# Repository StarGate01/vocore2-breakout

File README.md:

# vocore2-breakout

KiCad breakout board for the VoCore2 module (MT7628AN SoC).

## JTAG Connector (J-Link EDU Mini)

J6 is a 2×5 1.27 mm pitch header wired to the standard 9-pin ARM Cortex debug connector used by the J-Link EDU Mini.

| Pin | Signal | Notes |
|-----|--------|-------|
| 1 | `+3V3` | VTref - sense only, do not power board from here |
| 2 | `JTAG_TMS` | MT7628 `GPIO41` / `EPHY_LED2_N_JTMS` |
| 3 | `GND` | |
| 4 | `JTAG_CLK` | MT7628 `GPIO40` / `EPHY_LED3_N_JTCLK` |
| 5 | `GND` | |
| 6 | `JTAG_TDO` | MT7628 `GPIO43` / `EPHY_LED0_N_JTDO` |
| 7 | NC | KEY position - no pin on J-Link EDU Mini |
| 8 | `JTAG_TDI` | MT7628 `GPIO42` / `EPHY_LED1_N_JTDI` |
| 9 | `JTAG_TRST` | MT7628 `GPIO39` / `EPHY_LED4_N_JTRST_N` |
| 10 | `RESET` | MT7628 pin 138 / `PORST_N` (system reset, active-low) |

### J-Link EDU Mini reset pin specialities

The J-Link EDU Mini uses the **9-pin Cortex-M variant** of the connector, not the full 20-pin JTAG header:

- **Pin 7** is a physical key (no pin present). Not connected.
- **Pin 9** is repurposed by Segger as **nTRST** (JTAG TAP reset, active-low). In the standard Cortex-M spec pin 9 is NC; Segger uses it to support targets that need hardware TRST. Wire to `JTRST_N` (`GPIO39`).
- **Pin 10** is **nRESET** (system reset, active-low). Wire to `PORST_N`.

`WDT_RST_N` (`GPIO37` / MT7628 pin 137) appears adjacent to `PORST_N` and `JTRST_N` on the VoCore2 right-side connector and was considered for pin 9.

The vendor's JTAG how-to uses `WDT_RST_N` as "TRST" in their OpenOCD `sysfsgpio` config. This works because their setup is one VoCore2 bit-banging GPIOs to debug another - the host just needs two GPIO outputs to toggle, and driving `WDT_RST_N` low from an external GPIO triggers a full chip reset which also resets the JTAG TAP. OpenOCD's `sysfsgpio` driver doesn't care what hardware the signal is physically connected to; it just toggles the GPIO.

The J-Link is a hardware probe that follows the ARM Cortex debug connector spec strictly: pin 9 (`nTRST`) is driven by J-Link silicon to reset *only the JTAG TAP*, and the probe asserts and de-asserts it independently during normal debug sessions. If pin 9 connects to `WDT_RST_N`, every `nTRST` assertion by the J-Link triggers a full watchdog system reset, killing the debug session. `WDT_RST_N` is also a chip *output* when the watchdog fires, so the J-Link driving it creates a bus conflict. `JTRST_N` (`GPIO39`) resets only the TAP and has no output driver conflict.

### Pull-up resistors

All five JTAG signals (`TMS`, `TCK`, `TDI`, `TDO`, `TRST`) need pull-ups to 3V3. `RESET` (`PORST_N`) does not need external pull-ups from the breakout.

### OpenOCD configuration

OpenOCD requires third-party target scripts for the MT7628 - the standard script directory does not include this SoC. Clone [mtk-openwrt/openocd-scripts](https://github.com/mtk-openwrt/openocd-scripts) and point `OPENOCD_SCRIPTS` at it. This provides `mt7628.cfg` along with the `cpu_pll_init` and `dram_init` TCL helpers needed to bring up the PLL and DDR2 after halting the CPU via JTAG.

```sh
openocd -f interface/jlink.cfg \
        -c "transport select jtag" \
        -c "adapter speed 100" \
        -c "reset_config trst_and_srst separate srst_nogate connect_assert_srst" \
        -f mt7628.cfg \
        -c "init" \
        -c "reset halt" \
        -c "wait_halt 10000"
```

`adapter speed 100` - the MT7628 PLL is not running at reset; the JTAG clock source is the raw 40 MHz crystal. 100 kHz is conservative enough to be reliable in that window.

`reset_config trst_and_srst separate srst_nogate connect_assert_srst` - `connect_assert_srst` holds SRST (PORST_N) asserted when OpenOCD first connects, keeping the system in reset while the JTAG TAP initializes. `srst_nogate` keeps TCK running during SRST so OpenOCD can set the `EJTAGBOOT` instruction before releasing SRST. When SRST releases, the CPU starts with EJTAGBOOT active, enters the EJTAG debug ROM, and halts before its first instruction.

## TXD1 JTAG mode selector

MT7628 `GPIO13` / `TXD1` (VoCore2 pad `PR01`) is sampled at power-on reset to determine whether the `EPHY_LED` pins (`GPIO39`–`GPIO43`) operate as Ethernet LEDs or as the JTAG interface.

| `TXD1` at boot | Mode |
|----------------|------|
| HIGH (3V3) | Normal - `EPHY_LED` pins as Ethernet LEDs, **JTAG disabled** |
| LOW (GND) | **JTAG enabled** - `EPHY_LED` pins as `TMS`/`TCK`/`TDI`/`TDO`/`TRST` |

`JP1` is a 3-pin jumper with 4.7 kΩ resistors on both options:

| `JP1` position | `TXD1` | JTAG |
|---------------|--------|------|
| 1-2 ("GPIO", default) | HIGH via `R1` (4K7 to `+3V3`) | Disabled |
| 2-3 ("JTAG") | LOW via `R2` (4K7 to `GND`) | **Enabled** |

Warning: JTAG mode breaks SD/eMMC on the EPHY pads.`TXD1` low (`DBG_JTAG_MODE=0`) does more than swap the `EPHY_LED` pins to JTAG, it puts the whole EPHY block into JTAG/debug state. If SD/eMMC is then muxed onto the EPHY pads ("IoT" mode, e.g. VoCore2's SD lines), the card stops responding. This is a hardware mutual-exclusion, not a software setting, JTAG and SD-on-EPHY cannot be used at the same time. Change the jumper after flashing to put the board into normal operation.

### VoCore2 module modification required

The stock VoCore2 module has **`R9` populated** (pull-up, 4.7 kΩ to 3V3) which holds `TXD1` high and disables JTAG. To use JTAG:

1. Remove `R9` from the VoCore2 module (eliminates the internal pull-up).
2. Set `JP` to position 2-3 on the breakout.

The breakout `JP` then has sole control over `TXD1` with no internal resistor fighting it. Leaving `R9` on the module while setting `JP` to 2-3 creates a voltage divider (~1.65 V, undefined logic level).

The original VoCore2 JTAG how-to describes moving `R9` to the `R6` footprint (a pull-down). With `R9` removed entirely and `JP` at 2-3, the effect is the same.

## Fabrication

Gerber files are in the `gerber/` directory and can be sent directly to a PCB manufacturer.

Before assembly, it is recommended to bake the VoCore2 module at 120 °C for at least 12 hours to drive out moisture. However it works just as well without.

The VoCore2 module must be reflowed using hot air, do not use a soldering iron. The DDR2 on the module is ESD-sensitive and iron leakage current can cause permanent damage. Reflow temperature must not exceed 260 °C for more than 10 seconds.

The resistors can be reflowed together with the VoCore2 module or soldered normally with an iron. The through-hole pin headers are soldered normally. Take special care with the JTAG header (J6): it uses a 1.27 mm pitch fine-pitch header where adjacent pins are easy to bridge accidentally. Inspect with a loupe or microscope after soldering.

## References

- [J-Link EDU Mini KB](https://kb.segger.com/J-Link_EDU_Mini)
- [9-pin JTAG/SWD connector](https://kb.segger.com/9-pin_JTAG/SWD_connector)
- [VoCore2 pinout](https://vocore.io/v2.html)
- [VoCore2 JTAG how-to](https://vonger.cn/?p=14897)

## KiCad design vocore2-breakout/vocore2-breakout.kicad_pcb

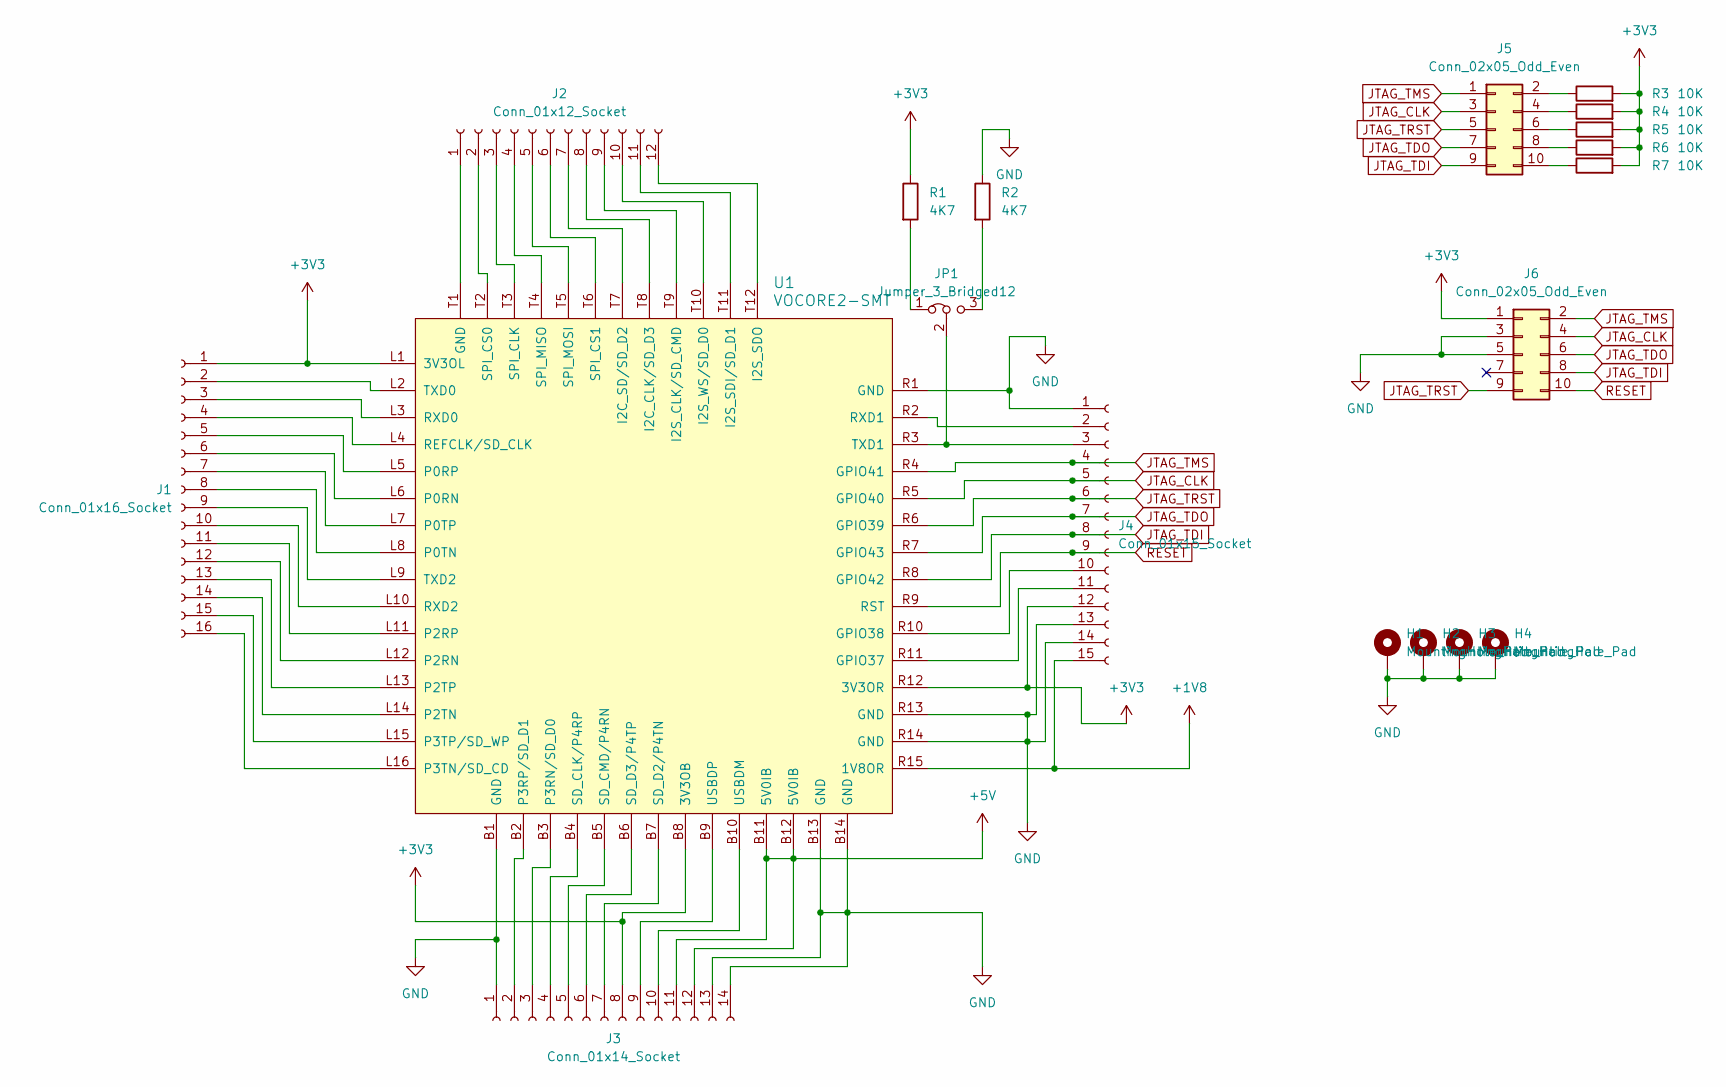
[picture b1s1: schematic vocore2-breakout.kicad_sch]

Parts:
H1, H2, H3, H4: MountingHole_Pad; MountingHole_3.2mm_M3_DIN965_Pad
J1: Conn_01x16_Socket; PinHeader_1x16_P2.54mm_Vertical
J2: Conn_01x12_Socket; PinHeader_1x12_P2.54mm_Vertical
J3: Conn_01x14_Socket; PinHeader_1x14_P2.54mm_Vertical
J4: Conn_01x15_Socket; PinHeader_1x15_P2.54mm_Vertical
J5: Conn_02x05_Odd_Even; PinHeader_2x05_P2.54mm_Vertical
J6: Conn_02x05_Odd_Even; PinHeader_2x05_P1.27mm_Vertical
JP1: Jumper_3_Bridged12; PinHeader_1x03_P2.54mm_Vertical
R1, R2: 4K7; R_0805_2012Metric_Pad1.20x1.40mm_HandSolder
R3, R4, R5, R6, R7: 10K; R_0805_2012Metric_Pad1.20x1.40mm_HandSolder
U1: VOCORE2-SMT

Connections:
+1V8: J4.15, U1.R15 (1V8OR)
+3V3: J1.1, J3.8, J4.12, J6.1, R1.1, R3.2, R4.2, R5.2, R6.2, R7.2, U1.B8 (3V3OB), U1.L1 (3V3OL), U1.R12 (3V3OR)
+5V: J3.11, J3.12, U1.B11 (5V0IB), U1.B12 (5V0IB)
GND: H1.1 (1_1), H2.1 (1_1), H3.1 (1_1), H4.1 (1_1), J3.1, J3.13, J3.14, J4.1, J4.13, J4.14, J6.3, J6.5, R2.1, U1.B1 (GND), U1.B13 (GND), U1.B14 (GND), U1.R1 (GND), U1.R13 (GND), U1.R14 (GND)
JTAG_CLK: J4.5, J5.3, J6.4, U1.R5 (GPIO40)
JTAG_TDI: J4.8, J5.9, J6.8, U1.R8 (GPIO42)
JTAG_TDO: J4.7, J5.7, J6.6, U1.R7 (GPIO43)
JTAG_TMS: J4.4, J5.1, J6.2, U1.R4 (GPIO41)
JTAG_TRST: J4.6, J5.5, J6.9, U1.R6 (GPIO39)
unnamed: J1.2, U1.L2 (TXD0)
unnamed: J1.3, U1.L3 (RXD0)
unnamed: J1.4, U1.L4 (REFCLK/SD_CLK)
unnamed: J1.5, U1.L5 (P0RP)
unnamed: J1.6, U1.L6 (P0RN)
unnamed: J1.7, U1.L7 (P0TP)
unnamed: J1.8, U1.L8 (P0TN)
unnamed: J1.9, U1.L9 (TXD2)
unnamed: J1.10, U1.L10 (RXD2)
unnamed: J1.11, U1.L11 (P2RP)
unnamed: J1.12, U1.L12 (P2RN)
unnamed: J1.13, U1.L13 (P2TP)
unnamed: J1.14, U1.L14 (P2TN)
unnamed: J1.15, U1.L15 (P3TP/SD_WP)
unnamed: J1.16, U1.L16 (P3TN/SD_CD)
unnamed: J2.1, U1.T1 (GND)
unnamed: J2.2, U1.T2 (SPI_CS0)
unnamed: J2.3, U1.T3 (SPI_CLK)
unnamed: J2.4, U1.T4 (SPI_MISO)
unnamed: J2.5, U1.T5 (SPI_MOSI)
unnamed: J2.6, U1.T6 (SPI_CS1)
unnamed: J2.7, U1.T7 (I2C_SD/SD_D2)
unnamed: J2.8, U1.T8 (I2C_CLK/SD_D3)
unnamed: J2.9, U1.T9 (I2S_CLK/SD_CMD)
unnamed: J2.10, U1.T10 (I2S_WS/SD_D0)
unnamed: J2.11, U1.T11 (I2S_SDI/SD_D1)
unnamed: J2.12, U1.T12 (I2S_SDO)
unnamed: J3.2, U1.B2 (P3RP/SD_D1)
unnamed: J3.3, U1.B3 (P3RN/SD_D0)
unnamed: J3.4, U1.B4 (SD_CLK/P4RP)
unnamed: J3.5, U1.B5 (SD_CMD/P4RN)
unnamed: J3.6, U1.B6 (SD_D3/P4TP)
unnamed: J3.7, U1.B7 (SD_D2/P4TN)
unnamed: J3.9, U1.B9 (USBDP)
unnamed: J3.10, U1.B10 (USBDM)
unnamed: J4.2, U1.R2 (RXD1)
unnamed: J4.3, JP1.2 (C), U1.R3 (TXD1)
unnamed: J4.10, U1.R10 (GPIO38)
unnamed: J4.11, U1.R11 (GPIO37)
unnamed: J5.2, R3.1
unnamed: J5.4, R4.1
unnamed: J5.6, R5.1
unnamed: J5.8, R6.1
unnamed: J5.10, R7.1
unnamed: JP1.1 (A), R1.2
unnamed: JP1.3 (B), R2.2
RESET: J4.9, J6.10, U1.R9 (RST)

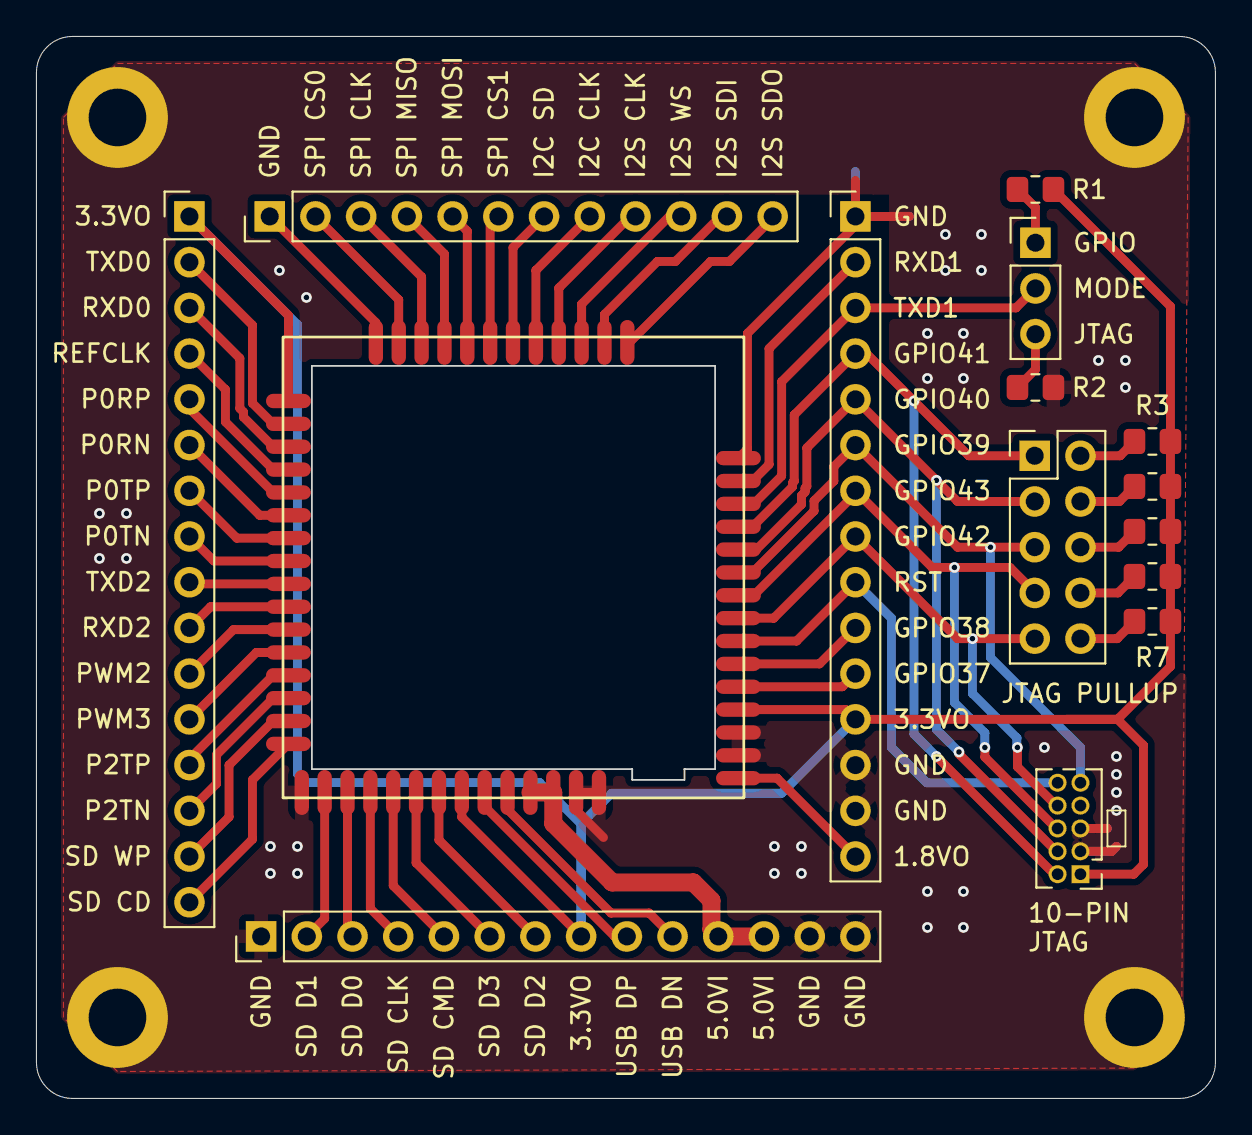
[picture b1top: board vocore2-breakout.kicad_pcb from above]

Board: 2 copper layers, 65.5 x 59.0 mm, 19 parts (0 on the bottom side), 56 nets.

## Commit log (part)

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2026-06-18 Add kicad files
2026-06-19 Use correct jtag reset
2026-06-19 Add readme
2026-06-22 Export gerber files
